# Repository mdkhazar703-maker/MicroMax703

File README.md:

# MacroMax703

A QMK-powered macro pad built around a Seeeduino XIAO, with a 3×3 switch matrix and two rotary encoders for volume and screen brightness. It also packs a hidden feature nobody outside this repo knows about yet.

## The Circuit Board

The heart of MacroMax703. This board is the platform that connects every part together into one seamless, clean-looking macro pad. At a glance it might look like a simple green rectangle, but it's actually packed with intricate wiring and several electronic components, forming a small, bustling network of data and electricity.
**[Click here for the KICanvas →](https://kicanvas.org/?repo=https%3A%2F%2Fgithub.com%2Fmdkhazar703-maker%2FMicroMax703%2Fblob%2Fmain%2Fpcb%2FMacroMax703_pcb.kicad_pro)**

*↑ The fine detailing that went into the routing.*

## The Case

To house this board properly, it needed a case worthy of it.

**[Click here for the case files on Printables →](https://www.printables.com/model/1764776-macromax)**

## The Firmware

Every piece of hardware needs a brain — ours runs on QMK Firmware.

## For the Curious

**Hardware**
- MCU: Seeeduino XIAO (SAMD21)
- Keys: 9× mechanical switches in a 3×3 matrix, 1× 1N4148 diode per switch
- Encoders: 2× rotary encoders with integrated push-button switches (SW10, SW11)

**Software**
- KiCad — PCB design
- Onshape — Case design
- QMK Firmware — Macro pad firmware development

<details>
<summary>Psst — about that hidden feature</summary>

We're not saying what it does here. Build one, dig through the firmware, and find out for yourself.

</details>

## Want to Make Your Own MacroMax703?

1. Install KiCad: https://www.kicad.org/download/
2. Open the schematics and get familiar with the circuit
3. Route your own PCB traces
4. Order and assemble your board
5. Download QMK Firmware and program your own macro pad

## Credits 

- Footprints of XIAO by hack Club Package
- Claude to explain and identify DRC issue of Thermal relief

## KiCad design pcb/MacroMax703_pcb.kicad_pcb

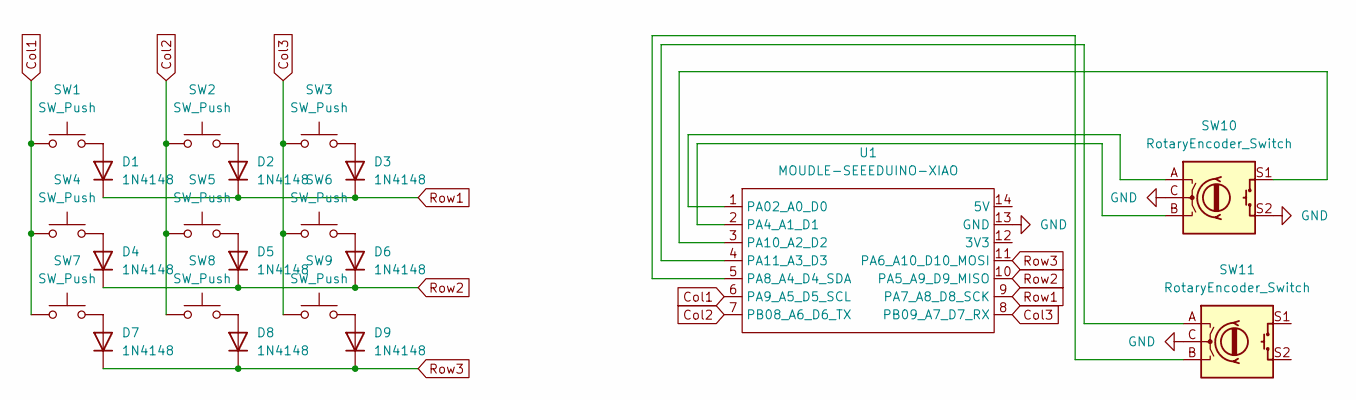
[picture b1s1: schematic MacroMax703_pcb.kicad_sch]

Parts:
D1, D2, D3, D4, D5, D6, D7, D8, D9: 1N4148; D_DO-35_SOD27_P7.62mm_Horizontal
SW1, SW2, SW3, SW4, SW5, SW6, SW7, SW8, SW9: SW_Push; SW_Cherry_MX_1.00u_PCB
SW10, SW11: RotaryEncoder_Switch; RotaryEncoder_Alps_EC11E-Switch_Vertical_H20mm
U1: MOUDLE-SEEEDUINO-XIAO; XIAO-Generic-Hybrid-14P-2.54-21X17.8MM

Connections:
Col1: SW1.1, SW4.1, SW7.1, U1.6 (PA9_A5_D5_SCL)
Col2: SW2.1, SW5.1, SW8.1, U1.7 (PB08_A6_D6_TX)
Col3: SW3.1, SW6.1, SW9.1, U1.8 (PB09_A7_D7_RX)
GND: SW10.C, SW10.S2, SW11.C, U1.13 (GND)
unnamed: D1.2 (A), SW1.2
unnamed: D2.2 (A), SW2.2
unnamed: D3.2 (A), SW3.2
unnamed: D4.2 (A), SW4.2
unnamed: D5.2 (A), SW5.2
unnamed: D6.2 (A), SW6.2
unnamed: D7.2 (A), SW7.2
unnamed: D8.2 (A), SW8.2
unnamed: D9.2 (A), SW9.2
unnamed: SW10.A, U1.1 (PA02_A0_D0)
unnamed: SW10.B, U1.2 (PA4_A1_D1)
unnamed: SW11.B, U1.5 (PA8_A4_D4_SDA)
unnamed: SW10.S1, U1.3 (PA10_A2_D2)
unnamed: SW11.A, U1.4 (PA11_A3_D3)
Row1: D1.1 (K), D2.1 (K), D3.1 (K), U1.9 (PA7_A8_D8_SCK)
Row2: D4.1 (K), D5.1 (K), D6.1 (K), U1.10 (PA5_A9_D9_MISO)
Row3: D7.1 (K), D8.1 (K), D9.1 (K), U1.11 (PA6_A10_D10_MOSI)

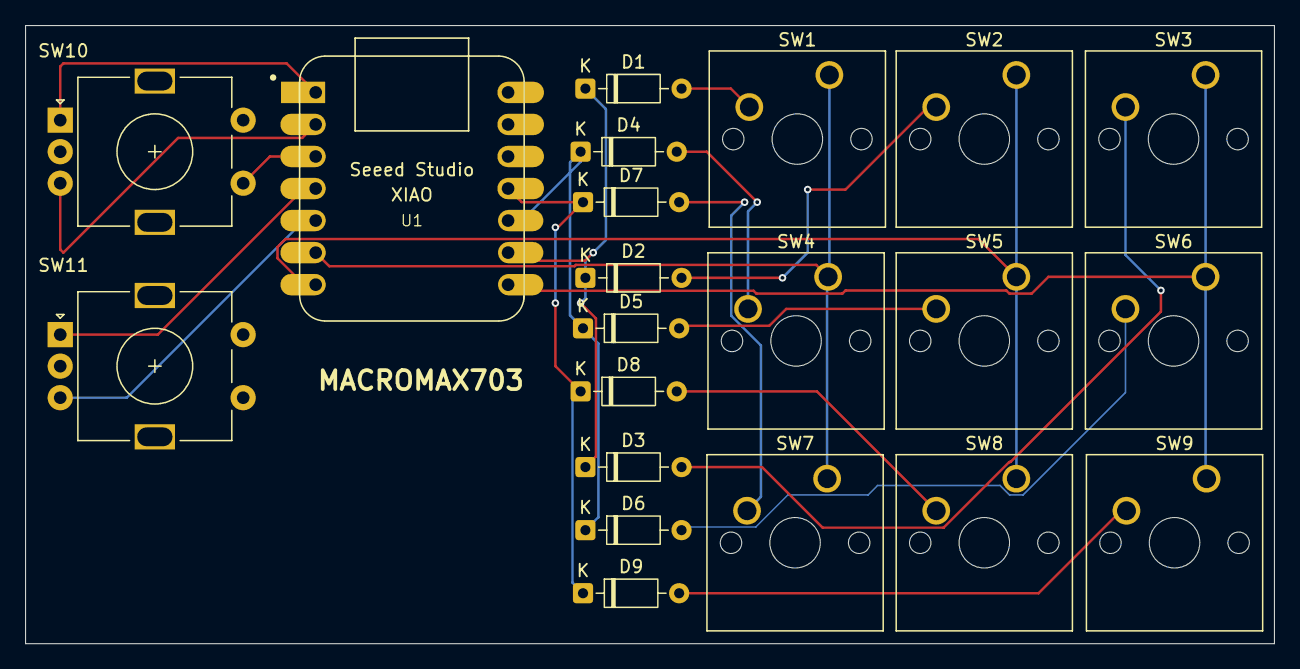
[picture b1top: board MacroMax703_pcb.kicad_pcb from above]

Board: 2 copper layers, 99.0 x 49.0 mm, 21 parts (0 on the bottom side), 21 nets.

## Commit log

2026-06-08 Initial test
2026-06-08 Led testing
2026-06-24 Initial Prototype for testing Purpouses
2026-06-24 Organisation
2026-06-24 fix: update pcb files
2026-06-25 update pcb and firmware
2026-06-25 update CAD file
2026-06-25 update production files
2026-06-25 update Firmware
2026-06-25 Enhance README with product details and hardware info
    Added detailed description and hardware specifications.
2026-06-25 amping up README
2026-06-25 Add images to README for visual enhancement
    Added an image to the README for better visual representation.
2026-06-25 Enhance README with detailed descriptions and images
    Expanded the README to include more details about the MacroMax703's circuit board, case, and firmware. Added images and corrected typos for clarity.
2026-06-25 Fix formatting in README for software tools
    Corrected formatting of tools used in the software section.
2026-06-25 Revise README.md for MacroMax703 project
    Updated project description and details about the MacroMax703, including sections on the circuit board, case, firmware, and hardware specifications.
2026-06-26 Update README with case files link and image
    Added a link to the case files on Printables and wrapped the image in a hyperlink.
2026-06-26 Add KICanvas link for MacroMax703 PCB
    Added a link to the KICanvas for the MacroMax703 PCB.
2026-06-26 Add credits section to README
    Added credits section with contributors and resources.
